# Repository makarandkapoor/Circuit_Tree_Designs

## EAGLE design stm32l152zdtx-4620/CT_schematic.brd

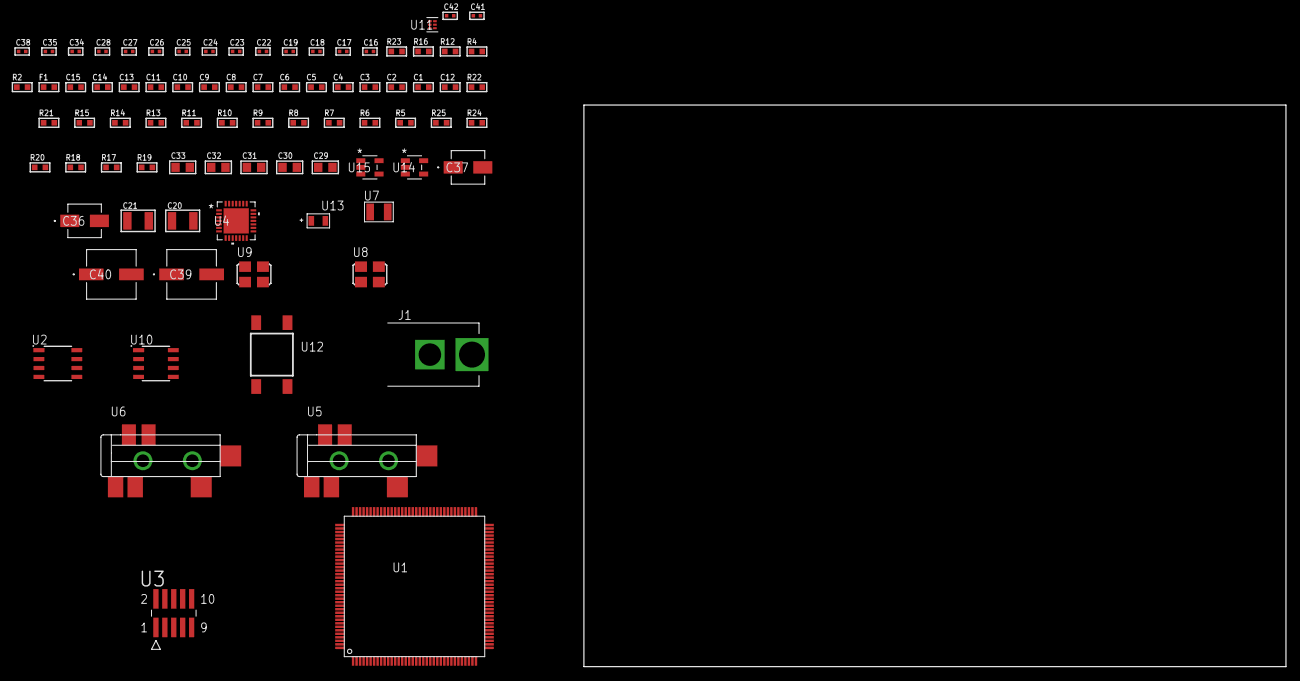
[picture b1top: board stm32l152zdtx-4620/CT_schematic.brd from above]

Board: 2 copper layers, 100.0 x 80.0 mm, 82 parts (0 on the bottom side), 37 nets, no tracks yet.

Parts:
C1, C2, C3, C4, C5, C6, C7, C8, C9, C10, C11, C13: 1e-07; C0603
C12: 4.7e-06; C0603
C14: 1e-08; C0603
C15: 1e-06; C0603
C16, C17: 1e-11; C0402
C18, C34, C35, C41, C42: 1e-08; C0402
C19, C24, C25, C26, C27, C28, C38: 1e-07; C0402
C20, C21: 2.2e-05; C1210
C22, C23: 1e-09; C0402
C29, C30, C31, C32, C33: 1e-05; C0805
C36: 1e-06; EXV-9B
C37: 2.2e-06; EXV-9B
C39, C40: 0.0001; EXV-9H
F1: 240.0; L0603
J1: PJ-037B; PJ-037B_PACKAGE
R2: 1000.0; R0603
R4: 4700.0; R0603
R5, R6, R7, R8, R9, R10, R11, R21, R22: 10000.0; R0603
R12: 5.0; R0603
R13, R14, R15: 47000.0; R0603
R16: 680.0; R0603
R17, R18, R20: 100000.0; R0603
R19: 164658.62; R0603
R23: 9100.0; R0603
R24: 680000.0; R0603
R25: 120000.0; R0603
U1: STM32L152ZDT6; LQFP144
U2: AT25512N-SH-T; SOIC-8
U3: FTSH-105-01-L-DV-K; SAMTEC_FTSH-105-01-L-DV-K
U4: WM8731CLSEFL; QFN-28
U5, U6: SJ-43515TS-SMT-TR
U7: ABS07-32.768KHZ-7-T
U8: ASFL1-12.288MHZ-EC-T; ASFL1
U9: ASFL1-25MHZ-NCS; ASFL1
U10: LP2954AIMX/NOPB; LP2954
U11: TPS3895ADRYR; SON-6
U12: 4-1437565-2; SW_4-1437565-2
U13: Q65110A2395; LGM67K-G1J2-24-Z
U14, U15: nc7sz125m5x; NC7SZ125M5X

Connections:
CLK_CRYSTAL_U1_8: C16.1, U1.8, U7.1
CLK_CRYSTAL_U1_9: C17.1, U1.9, U7.2
CLK_U1_23: U1.23, U9.3
CLK_U4_1: U4.1, U8.3
GND: C1.2, C2.2, C3.2, C4.2, C5.2, C6.2, C7.2, C8.2, C9.2, C10.2, C11.2, C12.2, C13.2, C14.2, C15.2, C16.2, C17.2, C18.2, C19.2, C23.2, C24.2, C25.2, C26.2, C27.2, C28.2, C29.2, C30.2, C31.2, C32.2, C33.2, C34.2, C35.2, C36.2, C37.2, C38.2, C39.2, C40.2, C41.2, C42.2, J1.2, R2.2, R5.2, R12.2, R13.2, R14.2, R15.2, R20.2, R23.2, R25.2, U1.16, U1.30, U1.31, U1.38, U1.51, U1.61, U1.71, U1.83, U1.94, U1.107, U1.120, U1.130, U1.143, U2.4, U3.3, U3.5, U4.4, U4.15, U4.19, U4.25, U4.26, U4.29, U5.1, U6.1, U8.2, U9.2, U10.4, U11.2, U13.C, U14.2, U14.3, U15.1, U15.3
NET_U1_6: C13.1, U1.6
NET_U1_25: R4.1, U1.25, U15.4
NET_U1_33: C14.1, C15.1, F1.1, U1.32, U1.33
NET_U1_138: R5.1, U1.138
NET_U1_142: U12.3, U12.4
NET_U2_3: R6.1, U2.3
NET_U2_7: R8.1, U2.7
NET_U3_9: R12.1, U3.9
NET_U4_20: C28.1, C33.1, U4.20
NET_U5_2: C21.1, R14.1, U5.2
NET_U5_5: C20.1, R13.1, U5.5
NET_U6_5: C22.1, C23.1, R15.1, R16.1, U6.5
NET_U10_3: R18.1, U10.3
NET_U10_5: R17.1, U10.5
NET_U10_7: R19.2, R20.1, U10.7
NET_U11_1: R22.1, R23.1, U11.1
NET_U11_3: R24.2, R25.1, U11.3
NET_U11_4: R21.1, U11.4, U14.4, U15.2
NET_U12_1: R2.1, U12.1, U12.2
PROC_I2S2_CK: U1.74, U4.7
PROC_I2S2_SD: U1.76, U4.8
PROC_I2S2_WS: U1.73, U4.9, U4.11
PROC_SPI1_MISO: U1.42, U2.2
PROC_SPI1_MOSI: U1.43, U2.5
PROC_SPI1_NSS: R7.1, U1.40, U2.1
PROC_SPI1_SCK: U1.41, U2.6
PROC_SYS_JTCK_SWCLK: R10.1, U1.109, U3.4
PROC_SYS_JTDO_TRACESWO: U1.133, U3.6
PROC_SYS_JTMS_SWDIO: R11.1, U1.105, U3.2
RST_OUT_U3_JTAG_RST_B: R9.1, U3.10, U14.1
VCC_S1_6V3: C36.1, C39.1, C40.1, J1.1, R18.2, U10.8
VCC_TIER1_3V3: C1.1, C2.1, C3.1, C4.1, C5.1, C6.1, C7.1, C8.1, C9.1, C10.1, C11.1, C12.1, C18.1, C19.1, C24.1, C25.1, C26.1, C27.1, C29.1, C30.1, C31.1, C32.1, C34.1, C35.1, C37.1, C38.1, C41.1, C42.1, F1.2, R4.2, R6.2, R7.2, R8.2, R9.2, R10.2, R11.2, R17.2, R19.1, R21.2, R22.2, R24.1, U1.17, U1.39, U1.52, U1.62, U1.72, U1.84, U1.95, U1.108, U1.121, U1.131, U1.144, U2.8, U3.1, U4.3, U4.5, U4.12, U4.18, U8.4, U9.4, U10.1, U11.6, U14.5, U15.5

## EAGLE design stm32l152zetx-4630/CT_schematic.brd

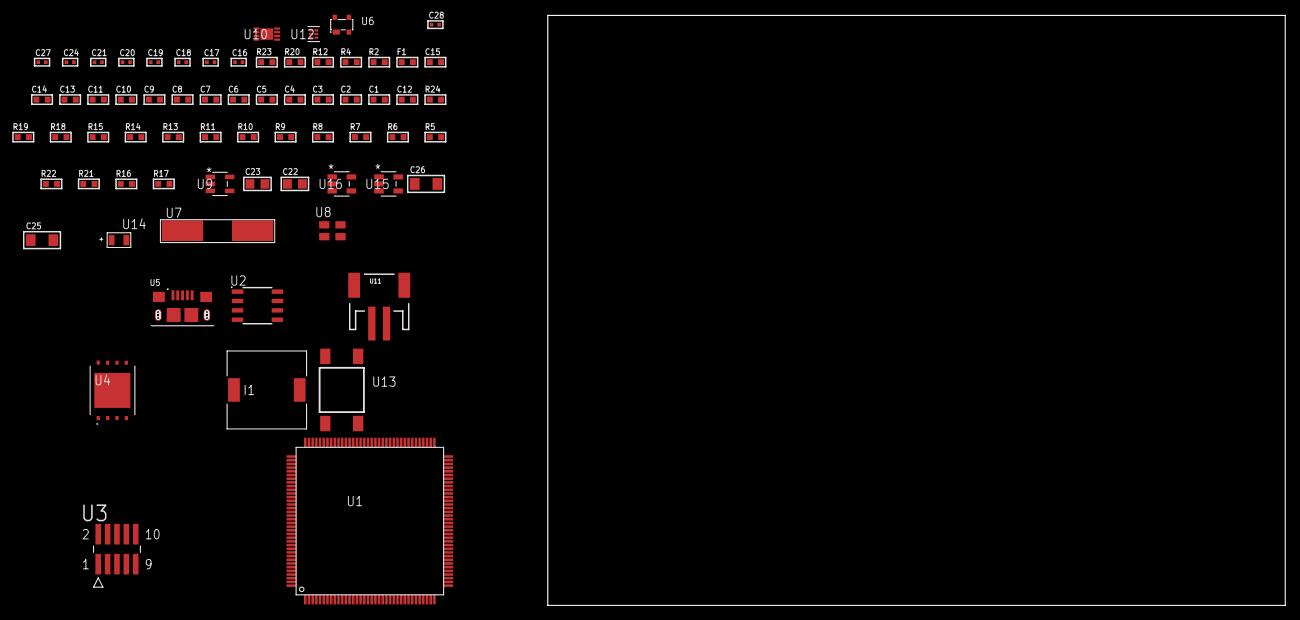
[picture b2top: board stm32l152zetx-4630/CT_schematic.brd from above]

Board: 2 copper layers, 68 parts (0 on the bottom side), 40 nets, no tracks yet.

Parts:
C1, C2, C3, C4, C5, C6, C7, C8, C9, C10, C11, C13: 1e-07; C0603
C12: 4.7e-06; C0603
C14: 1e-08; C0603
C15: 1e-06; C0603
C16, C17: 1e-11; C0402
C18, C20, C21, C27, C28: 1e-08; C0402
C19, C24: 1e-07; C0402
C22, C23: 1e-05; C0805
C25, C26: 1e-05; C1206
F1: 240.0; L0603
I1: 3.8e-06; DR1040
R2: 1000.0; R0603
R4: 4700.0; R0603
R5, R6, R7, R8, R9, R10, R11, R13, R14, R15, R18, R19, R24: 10000.0; R0603
R12: 5.0; R0603
R16: 220000.0; R0603
R17: 1000000.0; R0603
R20: 9100.0; R0603
R21: 680000.0; R0603
R22: 120000.0; R0603
R23: 2000.0; R0603
U1: STM32L152ZET6; LQFP144
U2: AT25080B-SSHL-T; SOIC-8
U3: FTSH-105-01-L-DV-K; SAMTEC_FTSH-105-01-L-DV-K
U4: S25FL128SDPNFI001; WNG008
U5: 10118193-0001LF; FCI_10118193-0001LF
U6: prtr5v0u2ax; SOT143B
U7: ABLS-25.000MHZ-B2F-T
U8: ASEK-32.768KHz-ECST; ASEK
U9: ltc3406es5; TSOT-23-5
U10: MCP73831T-2ACI/MC; DFN8_2X3MC
U11: S2B-PH-SM4-TB(LF)(SN); JST-2-SMD
U12: TPS3895ADRYR; SON-6
U13: 4-1437565-2; SW_4-1437565-2
U14: Q65110A2395; LGM67K-G1J2-24-Z
U15, U16: nc7sz125m5x; NC7SZ125M5X

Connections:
CLK_CRYSTAL_U1_23: C16.1, U1.23, U7.1
CLK_CRYSTAL_U1_24: C17.1, U1.24, U7.2
CLK_U1_8: U1.8, U8.3
GND: C1.2, C2.2, C3.2, C4.2, C5.2, C6.2, C7.2, C8.2, C9.2, C10.2, C11.2, C12.2, C13.2, C14.2, C15.2, C16.2, C17.2, C18.2, C19.2, C20.2, C21.2, C22.2, C23.1, C23.2, C24.2, C25.2, C26.2, C27.2, C28.2, R2.2, R5.2, R12.2, R16.2, R20.2, R22.2, R23.2, U1.16, U1.30, U1.31, U1.38, U1.51, U1.61, U1.71, U1.83, U1.94, U1.107, U1.120, U1.130, U1.143, U2.4, U3.3, U3.5, U4.4, U4.PAD, U5.5, U5.6, U5.7, U5.8, U5.9, U6.1, U8.2, U9.2, U10.6, U10.9, U11.2, U12.2, U14.C, U15.2, U15.3, U16.1, U16.3
INPUT_USBPOWER_5V: C25.1, R24.2, U5.1, U6.4, U10.1, U10.2
NET_U1_6: C13.1, U1.6
NET_U1_25: R4.1, U1.25, U16.4
NET_U1_33: C14.1, C15.1, F1.1, U1.32, U1.33
NET_U1_138: R5.1, U1.138
NET_U1_142: U13.3, U13.4
NET_U2_3: R6.1, U2.3
NET_U2_7: R8.1, U2.7
NET_U3_9: R12.1, U3.9
NET_U4_3: R13.1, U4.3
NET_U4_7: R15.1, U4.7
NET_U9_3: I1.1, U9.3
NET_U9_5: R16.1, R17.1, U9.5
NET_U9_ATNET_3: I1.2, R17.2
NET_U10_5: R24.1, U10.5
NET_U10_8: R23.1, U10.8
NET_U12_1: R19.1, R20.1, U12.1
NET_U12_3: R21.2, R22.1, U12.3
NET_U12_4: R18.1, U12.4, U15.4, U16.2
NET_U13_1: R2.1, U13.1, U13.2
PROC_SPI1_MISO: U1.42, U2.2
PROC_SPI1_MOSI: U1.43, U2.5
PROC_SPI1_NSS: R7.1, U1.40, U2.1
PROC_SPI1_SCK: U1.41, U2.6
PROC_SPI2_MISO: U1.75, U4.2
PROC_SPI2_MOSI: U1.76, U4.5
PROC_SPI2_NSS: R14.1, U1.73, U4.1
PROC_SPI2_SCK: U1.74, U4.6
PROC_SYS_JTCK_SWCLK: R10.1, U1.109, U3.4
PROC_SYS_JTDO_TRACESWO: U1.133, U3.6
PROC_SYS_JTMS_SWDIO: R11.1, U1.105, U3.2
PROC_USB_DM: U1.103, U5.2, U6.3
PROC_USB_DP: U1.104, U5.3, U6.2
RST_OUT_U3_JTAG_RST_B: R9.1, U3.10, U15.1
VCC_S1_3V7: C22.1, C26.1, U9.4, U10.3, U10.4, U11.1
VCC_TIER1_3V3: C1.1, C2.1, C3.1, C4.1, C5.1, C6.1, C7.1, C8.1, C9.1, C10.1, C11.1, C12.1, C18.1, C19.1, C20.1, C21.1, C23.2, C24.1, C27.1, C28.1, F1.2, I1.2, R4.2, R6.2, R7.2, R8.2, R9.2, R10.2, R11.2, R13.2, R14.2, R15.2, R17.2, R18.2, R19.2, R21.1, U1.17, U1.39, U1.52, U1.62, U1.72, U1.84, U1.95, U1.108, U1.121, U1.131, U1.144, U2.8, U3.1, U4.8, U8.4, U12.6, U15.5, U16.5

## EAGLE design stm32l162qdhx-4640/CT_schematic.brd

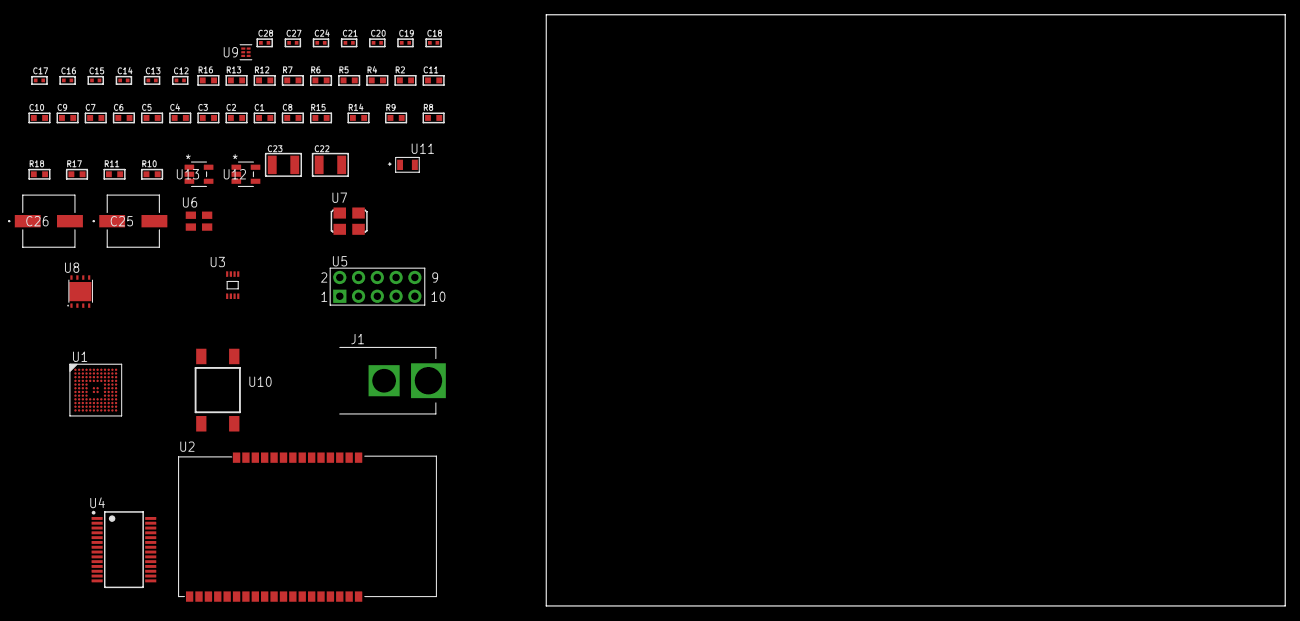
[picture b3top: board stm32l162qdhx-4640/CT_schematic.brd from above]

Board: 2 copper layers, 100.0 x 80.0 mm, 58 parts (0 on the bottom side), 35 nets, no tracks yet.

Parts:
C1, C2, C3, C4, C5, C6, C7, C9: 1e-07; C0603
C8: 4.7e-06; C0603
C10: 1e-08; C0603
C11: 1e-06; C0603
C12, C14, C15, C16, C17, C18, C24: 1e-07; C0402
C13, C19, C20, C21, C27, C28: 1e-08; C0402
C22, C23: 1e-05; C1210
C25, C26: 0.0001; EXV-9H
J1: PJ-037B; PJ-037B_PACKAGE
R2, R13: 1000.0; R0603
R4, R5: 4700.0; R0603
R6, R7: 2200.0; R0603
R8, R9, R14, R15: 10000.0; R0603
R10, R11: 100000.0; R0603
R12: 2231.0; R0603
R16: 9100.0; R0603
R17: 680000.0; R0603
R18: 120000.0; R0603
U1: STM32L162QDH6; UFBGA132
U2: ETRX3587
U3: 24AA08T-I/MNY; TDFN-8/6MM
U4: ST3241EBPR; SSOP-28
U5: HTSS-105-01-G-D
U6: ASEK-32.768KHz-ECST; ASEK
U7: ASFL1-25MHZ-NCS; ASFL1
U8: LP3878SDX-ADJ/NOPB; WSON-8
U9: TPS3895ADRYR; SON-6
U10: 4-1437565-2; SW_4-1437565-2
U11: Q65110A2395; LGM67K-G1J2-24-Z
U12, U13: nc7sz125m5x; NC7SZ125M5X

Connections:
CLK_U1_D1: U1.D1, U6.3
CLK_U1_F1: U1.F1, U7.3
GND: C1.2, C2.2, C3.2, C4.2, C5.2, C6.2, C7.2, C8.2, C9.2, C10.2, C11.2, C12.2, C13.2, C14.2, C17.2, C18.2, C19.2, C20.2, C21.2, C22.2, C23.2, C24.2, C25.2, C26.2, C27.2, C28.2, J1.2, R2.2, R8.2, R9.2, R13.2, R16.2, R18.2, U1.D3, U1.E3, U1.F2, U1.F6, U1.F7, U1.F11, U1.F12, U1.J1, U2.1, U2.13, U2.19, U2.20, U2.31, U2.33, U3.4, U4.23, U4.25, U5.9, U6.2, U7.2, U8.3, U8.PAD, U9.2, U11.C, U12.1, U12.3, U13.1, U13.3
NET_U1_A3: R6.1, U1.A3, U3.6
NET_U1_A4: R8.1, U1.A4
NET_U1_B3: R7.1, U1.B3, U3.5
NET_U1_E2: C9.1, U1.E2
NET_U1_H2: R5.1, U1.H2, U13.4
NET_U1_M12: U10.3, U10.4
NET_U2_7: R4.1, U2.7, U12.4
NET_U2_21: R9.1, U2.21
NET_U4_1: C16.1, U4.1
NET_U4_2: C16.2, U4.2
NET_U4_3: C18.1, U4.3
NET_U4_22: R10.1, U4.22
NET_U4_24: C15.2, U4.24
NET_U4_27: C17.1, U4.27
NET_U4_28: C15.1, U4.28
NET_U5_3: U4.4, U5.3
NET_U5_4: U4.5, U5.4
NET_U5_5: U4.9, U5.5
NET_U5_6: U4.10, U5.6
NET_U8_1: C21.1, U8.1
NET_U8_6: R12.2, R13.1, U8.6
NET_U8_8: R11.1, U8.8
NET_U9_1: R15.1, R16.1, U9.1
NET_U9_3: R17.2, R18.1, U9.3
NET_U9_4: R14.1, U9.4, U12.2, U13.2
NET_U10_1: R2.1, U10.1, U10.2
PROC_UART4_RX: U1.C10, U2.17
PROC_UART4_TX: U1.B11, U2.18
PROC_UART5_RX: U1.C8, U4.19
PROC_UART5_TX: U1.B10, U4.14
VCC_S1_14V8: C22.1, C25.1, C26.1, J1.1, R11.2, U8.4
VCC_TIER1_3V3: C1.1, C2.1, C3.1, C4.1, C5.1, C6.1, C7.1, C8.1, C10.1, C11.1, C12.1, C13.1, C14.1, C19.1, C20.1, C23.1, C24.1, C27.1, C28.1, R4.2, R5.2, R6.2, R7.2, R10.2, R12.1, R14.2, R15.2, R17.1, U1.C4, U1.G2, U1.G6, U1.G7, U1.G11, U1.G12, U1.H3, U1.L1, U1.M1, U2.32, U3.7, U3.8, U4.26, U6.4, U7.4, U8.5, U9.6, U12.5, U13.5

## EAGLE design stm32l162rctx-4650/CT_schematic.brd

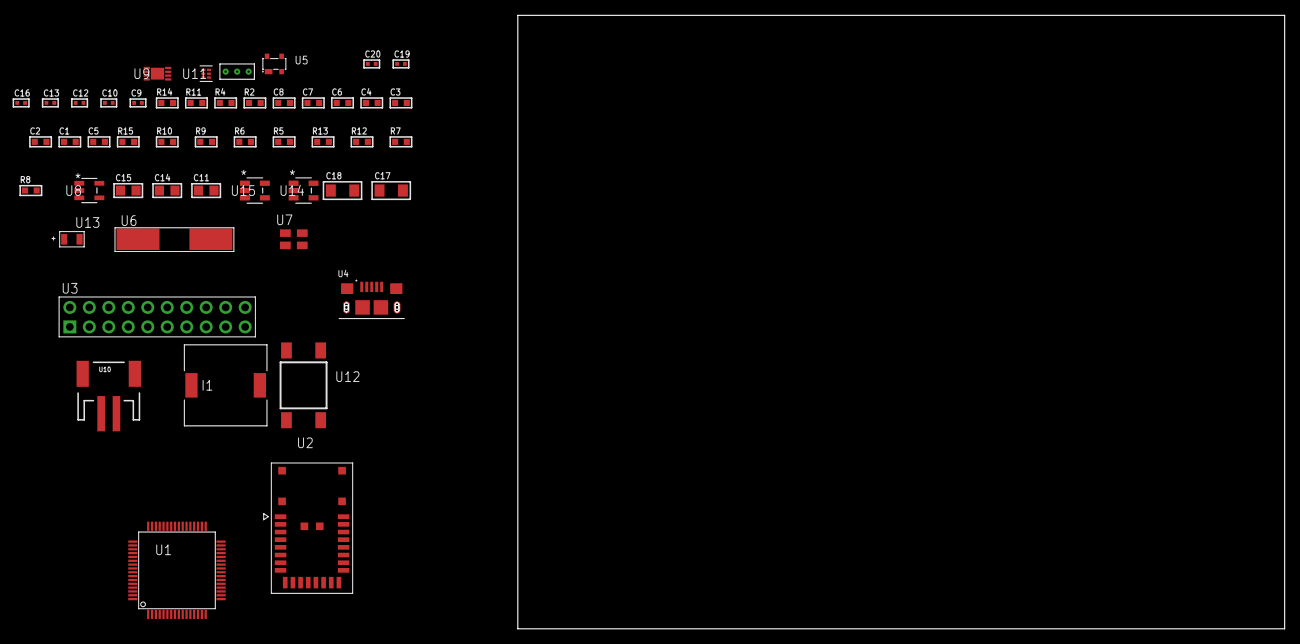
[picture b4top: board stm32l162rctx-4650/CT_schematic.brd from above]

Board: 2 copper layers, 122.6 x 80.0 mm, 50 parts (0 on the bottom side), 32 nets, no tracks yet.

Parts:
C1, C2, C3, C4, C6: 1e-07; C0603
C5: 4.7e-06; C0603
C7: 1e-08; C0603
C8: 1e-06; C0603
C9, C10: 1e-11; C0402
C11, C14, C15: 1e-05; C0805
C12, C16: 1e-07; C0402
C13, C19, C20: 1e-08; C0402
C17, C18: 1e-05; C1206
I1: 3.8e-06; DR1040
R2: 1000.0; R0603
R4: 4700.0; R0603
R5, R6, R9, R10, R15: 10000.0; R0603
R7: 220000.0; R0603
R8: 1000000.0; R0603
R11: 9100.0; R0603
R12: 680000.0; R0603
R13: 120000.0; R0603
R14: 2000.0; R0603
U1: STM32L162RCT6; LQFP64
U2: A2500R24A00GM
U3: TST-110-05-T-D-RA
U4: 10118193-0001LF; FCI_10118193-0001LF
U5: prtr5v0u2ax; SOT143B
U6: ABLS-25.000MHZ-B2F-T
U7: ASEK-32.768KHz-ECST; ASEK
U8: ltc3406es5; TSOT-23-5
U9: MCP73831T-2ACI/MC; DFN8_2X3MC
U10: S2B-PH-SM4-TB(LF)(SN); JST-2-SMD
U11: TPS3895ADRYR; SON-6
U12: 4-1437565-2; SW_4-1437565-2
U13: Q65110A2395; LGM67K-G1J2-24-Z
U14, U15: nc7sz125m5x; NC7SZ125M5X
U16: Dummy; DUMMY_PACKAGE_112

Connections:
CLK_CRYSTAL_U1_5: C9.1, U1.5, U6.1
CLK_CRYSTAL_U1_6: C10.1, U1.6, U6.2
CLK_U1_3: U1.3, U7.3
GND: C1.2, C2.2, C3.2, C4.2, C5.2, C6.2, C7.2, C8.2, C9.2, C10.2, C11.2, C12.2, C13.2, C14.2, C15.1, C15.2, C16.2, C17.2, C18.2, C19.2, C20.2, R2.2, R5.2, R7.2, R11.2, R13.2, R14.2, U1.12, U1.18, U1.31, U1.47, U1.63, U2.8, U2.17, U3.4, U3.6, U3.8, U3.10, U3.12, U3.14, U3.16, U3.18, U3.20, U4.5, U4.6, U4.7, U4.8, U4.9, U5.1, U7.2, U8.2, U9.6, U9.9, U10.2, U11.2, U13.C, U14.2, U14.3, U15.1, U15.3, U16.1
INPUT_USBPOWER_5V: C17.1, R15.2, U4.1, U5.4, U9.1, U9.2
NET_U1_1: C6.1, U1.1
NET_U1_7: R4.1, U1.7, U15.4
NET_U1_60: R5.1, U1.60
NET_U1_62: U12.3, U12.4
NET_U8_3: I1.1, U8.3
NET_U8_5: R7.1, R8.1, U8.5
NET_U8_ATNET_3: I1.2, R8.2
NET_U9_5: R15.1, U9.5
NET_U9_8: R14.1, U9.8
NET_U11_1: R10.1, R11.1, U11.1
NET_U11_3: R12.2, R13.1, U11.3
NET_U11_4: R9.1, U11.4, U14.4, U15.2
NET_U12_1: R2.1, U12.1, U12.2
PROC_PC13_WKUP2: U1.2, U16.2
PROC_PC15_OSC32_OUT: U1.4, U16.3
PROC_SPI1_MISO: U1.22, U2.10
PROC_SPI1_MOSI: U1.23, U2.11
PROC_SPI1_NSS: U1.20, U2.12
PROC_SPI1_SCK: U1.21, U2.9
PROC_SYS_JTCK_SWCLK: U1.49, U3.9
PROC_SYS_JTDO_TRACESWO: U1.55, U3.13
PROC_SYS_JTMS_SWDIO: U1.46, U3.7
PROC_USB_DM: U1.44, U4.2, U5.3
PROC_USB_DP: U1.45, U4.3, U5.2
RST_OUT_U3_SRESET_B: R6.1, U3.15, U14.1
VCC_S1_3V7: C14.1, C18.1, U8.4, U9.3, U9.4, U10.1
VCC_TIER1_3V3: C1.1, C2.1, C3.1, C4.1, C5.1, C7.1, C8.1, C11.1, C12.1, C13.1, C15.2, C16.1, C19.1, C20.1, I1.2, R4.2, R6.2, R8.2, R9.2, R10.2, R12.1, U1.13, U1.19, U1.32, U1.48, U1.64, U2.18, U3.1, U7.4, U11.6, U14.5, U15.5

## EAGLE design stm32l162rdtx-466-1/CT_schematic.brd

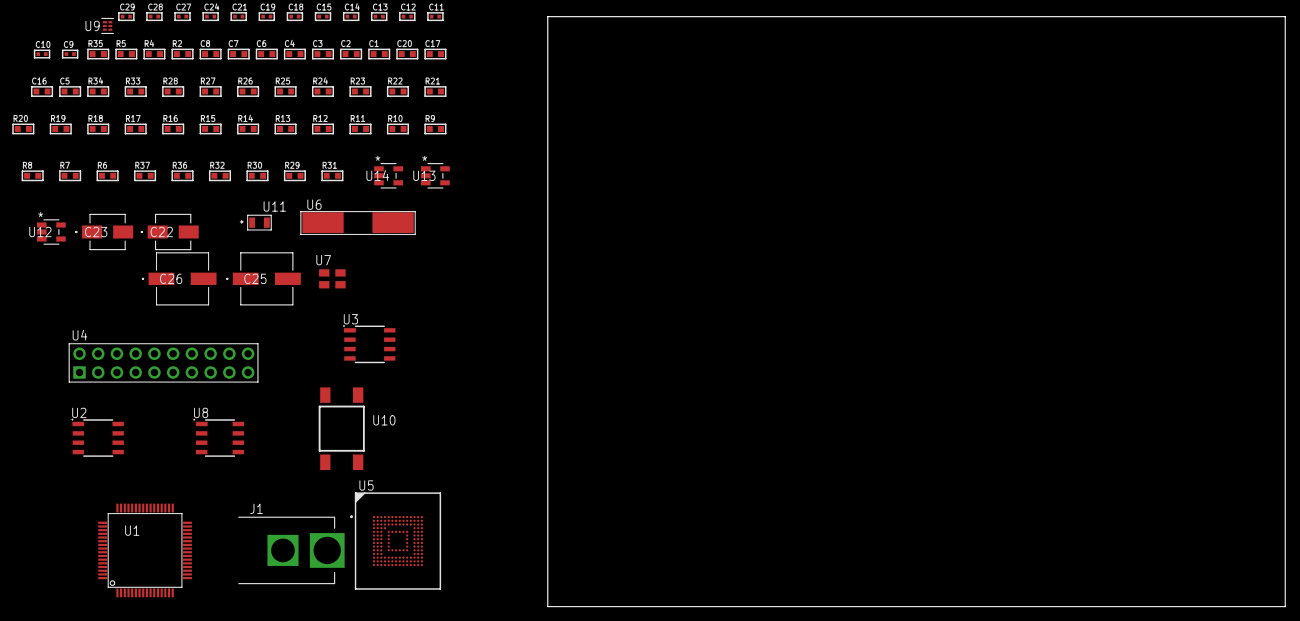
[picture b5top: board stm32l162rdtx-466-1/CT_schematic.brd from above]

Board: 2 copper layers, 100.0 x 80.0 mm, 79 parts (0 on the bottom side), 45 nets, no tracks yet.

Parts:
C1, C2, C3, C4, C6: 1e-07; C0603
C5: 4.7e-06; C0603
C7: 1e-08; C0603
C8: 1e-06; C0603
C9, C10: 1e-11; C0402
C11, C12, C21, C27, C28, C29: 1e-08; C0402
C13, C14, C15, C18, C19, C24: 1e-07; C0402
C16, C17, C20: 2.2e-06; C0603
C22: 1e-06; EXV-9B
C23: 2.2e-06; EXV-9B
C25, C26: 0.0001; EXV-9H
J1: PJ-037B; PJ-037B_PACKAGE
R2: 1000.0; R0603
R4, R5: 4700.0; R0603
R6, R7, R8, R9, R10, R11, R12, R13, R14, R15, R16, R17, R18, R33, R34: 10000.0; R0603
R19, R20, R21, R22, R23, R24, R25, R26, R27, R28: 34000.0; R0603
R29, R30, R32: 100000.0; R0603
R31: 164658.62; R0603
R35: 9100.0; R0603
R36: 680000.0; R0603
R37: 120000.0; R0603
U1: STM32L162RDT6; LQFP64
U2: AT25080B-SSHL-T; SOIC-8
U3: AT25128B-SSHL-T; SOIC-8
U4: TST-110-05-T-D-RA
U5: mtfc4gmcdm; TFBGA-153
U6: ABLS-25.000MHZ-B2F-T
U7: ASEK-32.768KHz-ECST; ASEK
U8: LP2954AIMX/NOPB; LP2954
U9: TPS3895ADRYR; SON-6
U10: 4-1437565-2; SW_4-1437565-2
U11: Q65110A2395; LGM67K-G1J2-24-Z
U12, U13, U14: nc7sz125m5x; NC7SZ125M5X

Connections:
CLK_CRYSTAL_U1_5: C9.1, U1.5, U6.1
CLK_CRYSTAL_U1_6: C10.1, U1.6, U6.2
CLK_U1_3: U1.3, U7.3
GND: C1.2, C2.2, C3.2, C4.2, C5.2, C6.2, C7.2, C8.2, C9.2, C10.2, C11.2, C12.2, C13.2, C14.2, C15.2, C16.2, C17.2, C18.2, C19.2, C20.2, C21.2, C22.2, C23.2, C24.2, C25.2, C26.2, C27.2, C28.2, C29.2, J1.2, R2.2, R6.2, R18.2, R32.2, R35.2, R37.2, U1.12, U1.18, U1.31, U1.47, U1.63, U2.4, U3.4, U4.4, U4.6, U4.8, U4.10, U4.12, U4.14, U4.16, U4.18, U4.20, U5.C4, U5.E7, U5.G5, U5.H10, U5.K8, U5.N2, U5.N5, U5.P4, U5.P6, U7.2, U8.4, U9.2, U11.C, U12.2, U12.3, U13.1, U13.3, U14.1, U14.3
NET_U1_1: C6.1, U1.1
NET_U1_7: R5.1, U1.7, U14.4
NET_U1_59: U10.3, U10.4
NET_U1_60: R6.1, U1.60
NET_U2_3: R7.1, U2.3
NET_U2_7: R9.1, U2.7
NET_U3_3: R10.1, U3.3
NET_U3_7: R12.1, U3.7
NET_U4_19: R18.1, U4.19
NET_U5_C2: C17.1, C18.1, U5.C2
NET_U5_K5: R4.1, U5.K5, U13.4
NET_U8_3: R30.1, U8.3
NET_U8_5: R29.1, U8.5
NET_U8_7: R31.2, R32.1, U8.7
NET_U9_1: R34.1, R35.1, U9.1
NET_U9_3: R36.2, R37.1, U9.3
NET_U9_4: R33.1, U9.4, U12.4, U13.2, U14.2
NET_U10_1: R2.1, U10.1, U10.2
PROC_SDIO_CK: R28.1, U1.53, U5.M6
PROC_SDIO_CMD: R27.1, U1.54, U5.M5
PROC_SDIO_D0: R19.1, U1.39, U5.A3
PROC_SDIO_D1: R20.1, U1.40, U5.A4
PROC_SDIO_D2: R21.1, U1.51, U5.A5
PROC_SDIO_D3: R22.1, U1.52, U5.B2
PROC_SDIO_D4: R23.1, U1.61, U5.B3
PROC_SDIO_D5: R24.1, U1.62, U5.B4
PROC_SDIO_D6: R25.1, U1.37, U5.B5
PROC_SDIO_D7: R26.1, U1.38, U5.B6
PROC_SPI1_MISO: U1.22, U3.2
PROC_SPI1_MOSI: U1.23, U3.5
PROC_SPI1_NSS: R11.1, U1.20, U3.1
PROC_SPI1_SCK: U1.21, U3.6
PROC_SPI2_NSS: R8.1, U2.1
PROC_SYS_JTCK_SWCLK: R16.1, U1.49, U4.9
PROC_SYS_JTDI: R14.1, U1.50, U4.5
PROC_SYS_JTDO_TRACESWO: U1.55, U4.13
PROC_SYS_JTMS_SWDIO: R15.1, U1.46, U4.7
PROC_SYS_JTRST: R13.1, U1.56, U4.3
RST_OUT_U4_SRESET_B: R17.1, U4.15, U12.1
VCC_S1_7V0: C22.1, C25.1, C26.1, J1.1, R30.2, U8.8
VCC_TIER1_3V3: C1.1, C2.1, C3.1, C4.1, C5.1, C7.1, C8.1, C11.1, C12.1, C13.1, C14.1, C15.1, C16.1, C19.1, C20.1, C21.1, C23.1, C24.1, C27.1, C28.1, C29.1, R4.2, R5.2, R7.2, R8.2, R9.2, R10.2, R11.2, R12.2, R13.2, R14.2, R15.2, R16.2, R17.2, R19.2, R20.2, R21.2, R22.2, R23.2, R24.2, R25.2, R26.2, R27.2, R28.2, R29.2, R31.1, R33.2, R34.2, R36.1, U1.13, U1.19, U1.32, U1.48, U1.64, U2.8, U3.8, U4.1, U4.2, U5.C6, U5.E6, U5.F5, U5.J10, U5.K9, U5.M4, U5.N4, U5.P3, U5.P5, U7.4, U8.1, U9.6, U12.5, U13.5, U14.5

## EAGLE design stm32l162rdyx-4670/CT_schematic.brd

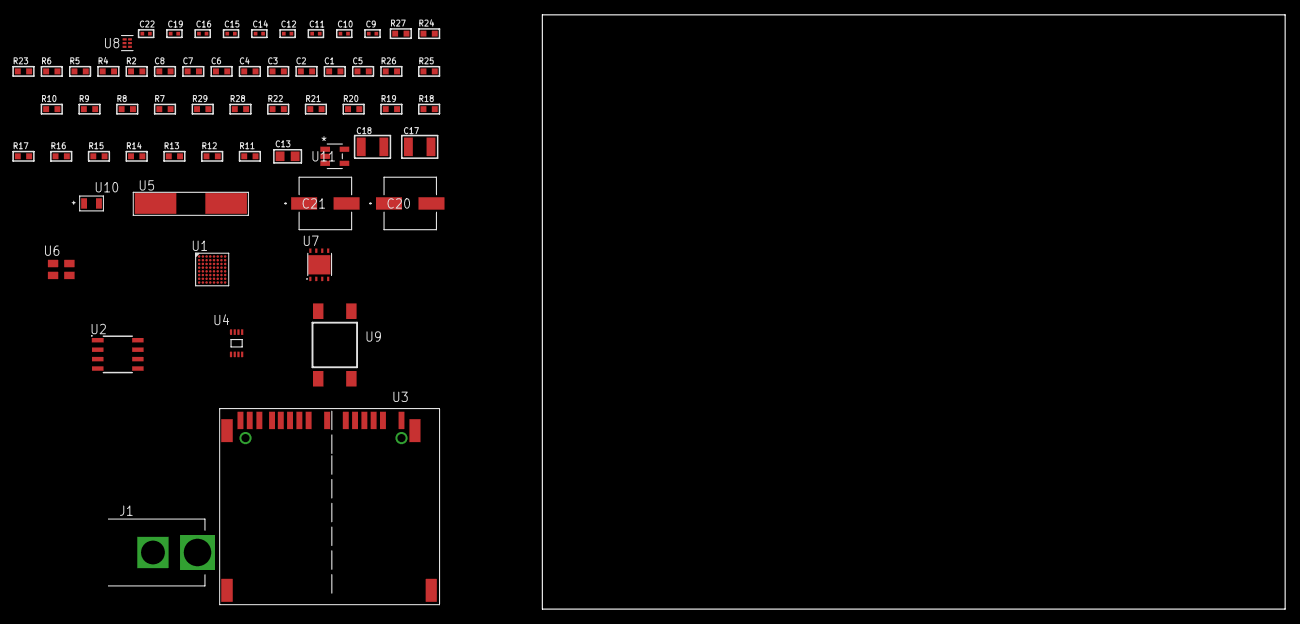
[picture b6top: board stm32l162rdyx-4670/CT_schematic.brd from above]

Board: 2 copper layers, 100.0 x 80.0 mm, 61 parts (0 on the bottom side), 37 nets, no tracks yet.

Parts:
C1, C2, C3, C4, C6: 1e-07; C0603
C5: 4.7e-06; C0603
C7: 1e-08; C0603
C8: 1e-06; C0603
C9, C10: 1e-11; C0402
C11, C14, C15, C16, C22: 1e-08; C0402
C12, C19: 1e-07; C0402
C13: 1e-05; C0805
C17, C18: 1e-05; C1210
C20, C21: 0.0001; EXV-9H
J1: PJ-037B; PJ-037B_PACKAGE
R2, R24: 1000.0; R0603
R4: 4700.0; R0603
R5, R6: 2200.0; R0603
R7, R8, R9, R10, R25, R26: 10000.0; R0603
R11, R12, R13, R14, R15, R16, R17, R18, R19, R20, R21, R22: 100000.0; R0603
R23: 2231.0; R0603
R27: 9100.0; R0603
R28: 680000.0; R0603
R29: 120000.0; R0603
U1: STM32L162RDY6; WLCSP64
U2: AT25010B-SSHL-T; SOIC-8
U3: 10100565
U4: 24AA04-I/MC; TDFN-8/6MM
U5: ABLS-25.000MHZ-B2F-T
U6: ASEK-32.768KHz-ECST; ASEK
U7: LP3878SDX-ADJ/NOPB; WSON-8
U8: TPS3895ADRYR; SON-6
U9: 4-1437565-2; SW_4-1437565-2
U10: Q65110A2395; LGM67K-G1J2-24-Z
U11: nc7sz125m5x; NC7SZ125M5X

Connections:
CLK_CRYSTAL_U1_D7: C9.1, U1.D7, U5.1
CLK_CRYSTAL_U1_D8: C10.1, U1.D8, U5.2
CLK_U1_B8: U1.B8, U6.3
GND: C1.2, C2.2, C3.2, C4.2, C5.2, C6.2, C7.2, C8.2, C9.2, C10.2, C11.2, C12.2, C13.2, C14.2, C15.2, C16.2, C17.2, C18.2, C19.2, C20.2, C21.2, C22.2, J1.2, R2.2, R7.2, R24.2, R27.2, R29.2, U1.A7, U1.B1, U1.E7, U1.F5, U1.H2, U2.4, U3.6, U3.10, U3.12, U3.16, U3.17, U3.20, U3.21, U4.4, U4.7, U6.2, U7.3, U7.PAD, U8.2, U10.C, U11.1, U11.3
NET_U1_A6: R7.1, U1.A6
NET_U1_B5: R5.1, U1.B5, U4.6
NET_U1_C5: R6.1, U1.C5, U4.5
NET_U1_C6: C6.1, U1.C6
NET_U1_C7: R4.1, U1.C7, U11.4
NET_U1_H8: U9.3, U9.4
NET_U2_3: R8.1, U2.3
NET_U2_7: R10.1, U2.7
NET_U3_1: R13.1, U3.1
NET_U3_2: R12.1, U3.2
NET_U3_18: U3.18, U3.19
NET_U7_1: C16.1, U7.1
NET_U7_6: R23.2, R24.1, U7.6
NET_U7_8: R22.1, U7.8
NET_U8_1: R26.1, R27.1, U8.1
NET_U8_3: R28.2, R29.1, U8.3
NET_U8_4: R25.1, U8.4, U11.2
NET_U9_1: R2.1, U9.1, U9.2
PROC_SDIO_CK: R11.1, U1.C4, U3.8
PROC_SDIO_D0: R14.1, U1.E3, U3.4
PROC_SDIO_D1: R15.1, U1.D1, U3.3
PROC_SDIO_D2: R16.1, U1.A2, U3.15
PROC_SDIO_D3: R17.1, U1.B3, U3.14
PROC_SDIO_D4: R18.1, U1.D5, U3.13
PROC_SDIO_D5: R19.1, U1.B6, U3.11
PROC_SDIO_D6: R20.1, U1.E1, U3.7
PROC_SDIO_D7: R21.1, U1.E2, U3.5
PROC_SPI1_MISO: U1.B4, U2.2
PROC_SPI1_MOSI: U1.A5, U2.5
PROC_SPI1_NSS: R9.1, U1.C3, U2.1
PROC_SPI1_SCK: U1.A4, U2.6
VCC_S1_12V8: C17.1, C20.1, C21.1, J1.1, R22.2, U7.4
VCC_TIER1_3V3: C1.1, C2.1, C3.1, C4.1, C5.1, C7.1, C8.1, C11.1, C12.1, C13.1, C14.1, C15.1, C18.1, C19.1, C22.1, R4.2, R5.2, R6.2, R8.2, R9.2, R10.2, R11.2, R12.2, R13.2, R14.2, R15.2, R16.2, R17.2, R18.2, R19.2, R20.2, R21.2, R23.1, R25.2, R26.2, R28.1, U1.A1, U1.A8, U1.G6, U1.G8, U1.H1, U2.8, U3.9, U4.8, U6.4, U7.5, U8.6, U11.5

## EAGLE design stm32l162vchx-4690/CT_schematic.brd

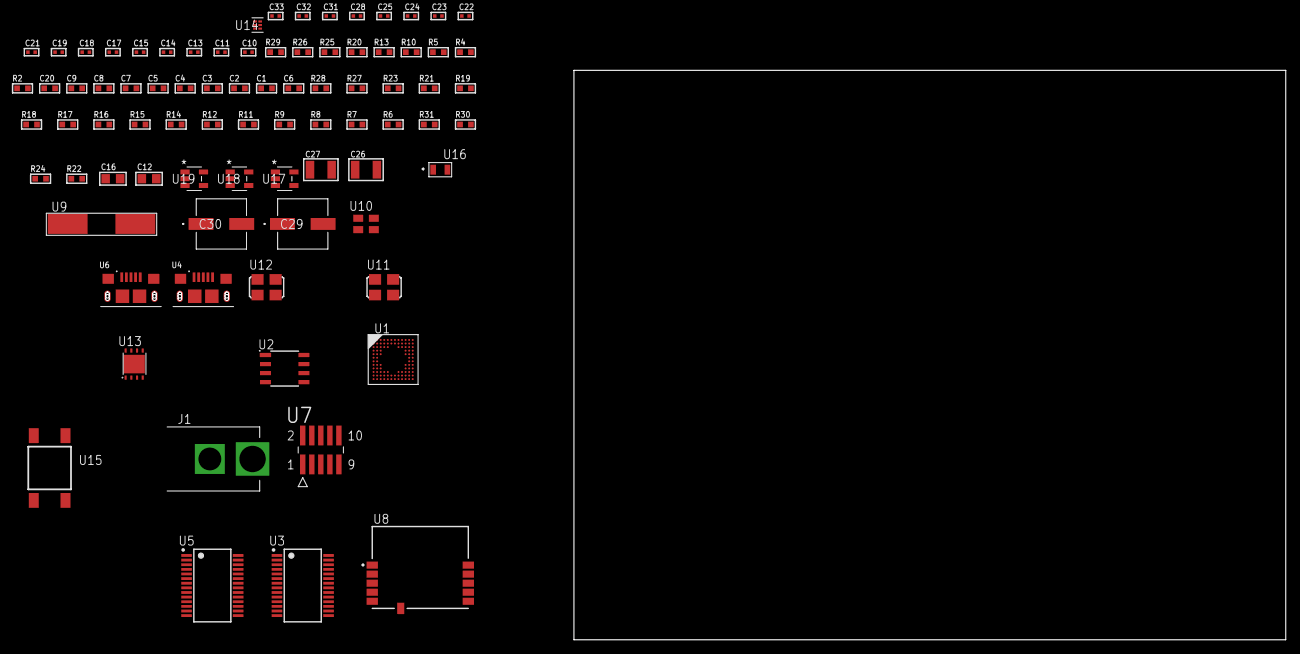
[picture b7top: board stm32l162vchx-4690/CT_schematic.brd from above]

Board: 2 copper layers, 82 parts (0 on the bottom side), 53 nets, no tracks yet.

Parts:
C1, C2, C3, C4, C5, C7: 1e-07; C0603
C6: 4.7e-06; C0603
C8: 1e-08; C0603
C9, C20: 1e-06; C0603
C10, C22, C23, C24, C25, C31, C32, C33: 1e-08; C0402
C11, C13, C14, C15, C17, C18, C19, C21, C28: 1e-07; C0402
C12, C16: 4.7e-06; C0805
C26, C27: 1e-05; C1210
C29, C30: 0.0001; EXV-9H
J1: PJ-037B; PJ-037B_PACKAGE
R2, R26: 1000.0; R0603
R4, R5, R10, R13: 4700.0; R0603
R6, R7, R8, R9, R11, R12, R14, R15, R16, R17, R18, R19, R21, R27, R28: 10000.0; R0603
R20: 5.0; R0603
R22, R24: 100000.0; R0603
R23: 47000.0; R0603
R25: 2231.0; R0603
R29: 9100.0; R0603
R30: 680000.0; R0603
R31: 120000.0; R0603
U1: STM32L162VCH6; UFBGA100
U2: AT25M02-SSHD-T; SOIC-8
U3, U5: FT232RL-REEL; SSOP-28
U4, U6: 10118193-0001LF; FCI_10118193-0001LF
U7: FTSH-105-01-L-DV-K; SAMTEC_FTSH-105-01-L-DV-K
U8: SPBTLE-RF; XCVR_SPBTLE-RF
U9: ABLS-12.000MHZ-B4-T
U10: ASEK-32.768KHz-ECST; ASEK
U11: ASFL1-12MHZ-NCS; ASFL1
U12: ASFL1-25MHZ-NCS; ASFL1
U13: LP3878SDX-ADJ/NOPB; WSON-8
U14: TPS3895ADRYR; SON-6
U15: 4-1437565-2; SW_4-1437565-2
U16: Q65110A2395; LGM67K-G1J2-24-Z
U17, U18, U19: nc7sz125m5x; NC7SZ125M5X

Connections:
CLK_CRYSTAL_U5_27: U5.27, U9.1
CLK_CRYSTAL_U5_28: U5.28, U9.2
CLK_U1_D1: U1.D1, U10.3
CLK_U1_F1: U1.F1, U12.3
CLK_U3_27: U3.27, U11.3
GND: C1.2, C2.2, C3.2, C4.2, C5.2, C6.2, C7.2, C8.2, C9.2, C10.2, C11.2, C12.2, C13.2, C14.2, C15.2, C16.2, C17.2, C18.2, C19.2, C20.2, C21.2, C22.2, C23.2, C24.2, C25.2, C26.2, C27.2, C28.2, C29.2, C30.2, C31.2, C32.2, C33.2, J1.2, R2.2, R6.2, R12.2, R15.2, R19.2, R20.2, R22.2, R23.2, R26.2, R29.2, R31.2, U1.D3, U1.E3, U1.F2, U1.F11, U1.F12, U1.J1, U1.K1, U2.4, U3.7, U3.18, U3.21, U3.25, U3.26, U4.5, U4.6, U4.7, U4.8, U4.9, U5.7, U5.18, U5.21, U5.25, U5.26, U6.5, U6.6, U6.7, U6.8, U6.9, U7.3, U7.5, U8.6, U10.2, U11.2, U12.2, U13.3, U13.PAD, U14.2, U16.C, U17.2, U17.3, U18.1, U18.3, U19.1, U19.3
NET_U1_A4: R6.1, U1.A4
NET_U1_E2: C7.1, U1.E2
NET_U1_H2: R5.1, U1.H2, U19.4
NET_U1_M12: U15.3, U15.4
NET_U2_3: R7.1, U2.3
NET_U2_7: R9.1, U2.7
NET_U3_14: R11.1, U3.14
NET_U3_17: C13.1, U3.17
NET_U3_19: R12.1, U3.19
NET_U4_1: R10.1, U4.1
NET_U4_2: U3.16, U4.2
NET_U4_3: U3.15, U4.3
NET_U5_14: R14.1, U5.14
NET_U5_17: C17.1, U5.17
NET_U5_19: R15.1, U5.19
NET_U6_1: R13.1, U6.1
NET_U6_2: U5.16, U6.2
NET_U6_3: U5.15, U6.3
NET_U7_9: R20.1, U7.9
NET_U8_11: R4.1, U8.11, U18.4
NET_U13_1: C25.1, U13.1
NET_U13_6: R25.2, R26.1, U13.6
NET_U13_8: R24.1, U13.8
NET_U14_1: R28.1, R29.1, U14.1
NET_U14_3: R30.2, R31.1, U14.3
NET_U14_4: R27.1, U14.4, U17.4, U18.2, U19.2
NET_U15_1: R2.1, U15.1, U15.2
PROC_GPIO_TO_U8_SPI_IRQ: R23.1, U1.A1, U8.4
PROC_SPI1_MISO: U1.A7, U8.8
PROC_SPI1_MOSI: U1.C5, U8.9
PROC_SPI1_NSS: R21.1, U1.L9, U8.10
PROC_SPI1_SCK: R22.1, U1.K4, U8.7
PROC_SPI2_MISO: U1.B8, U2.2
PROC_SPI2_MOSI: U1.B7, U2.5
PROC_SPI2_NSS: R8.1, U1.C9, U2.1
PROC_SPI2_SCK: U1.B9, U2.6
PROC_SYS_JTCK_SWCLK: R19.1, U1.A10, U7.4
PROC_SYS_JTDI: R17.1, U1.A9, U7.8
PROC_SYS_JTDO_TRACESWO: U1.A8, U7.6
PROC_SYS_JTMS_SWDIO: R18.1, U1.A11, U7.2
PROC_USART1_CTS: U1.B12, U3.3
PROC_USART1_RTS: U1.A12, U3.11
PROC_USART1_RX: U1.B4, U3.1
PROC_USART1_TX: U1.B5, U3.5
RST_OUT_U7_JTAG_RST_B: R16.1, U7.10, U17.1
VCC_S1_15V0: C26.1, C29.1, C30.1, J1.1, R24.2, U13.4
VCC_TIER1_3V3: C1.1, C2.1, C3.1, C4.1, C5.1, C6.1, C8.1, C9.1, C10.1, C11.1, C12.1, C14.1, C15.1, C16.1, C18.1, C19.1, C20.1, C21.1, C22.1, C23.1, C24.1, C27.1, C28.1, C31.1, C32.1, C33.1, R4.2, R5.2, R7.2, R8.2, R9.2, R11.2, R14.2, R16.2, R17.2, R18.2, R21.2, R25.1, R27.2, R28.2, R30.1, U1.C4, U1.G2, U1.G11, U1.G12, U1.H3, U1.L1, U1.M1, U2.8, U3.4, U3.20, U5.4, U5.20, U7.1, U8.5, U10.4, U11.4, U12.4, U13.5, U14.6, U17.5, U18.5, U19.5
